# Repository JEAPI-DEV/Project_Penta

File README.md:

## Schematic and PCB Layers

- [Schematic](files/schematic.pdf)
- [PCB Front](files/pcbF.pdf)
- [PCB Back](files/pcbB.pdf)
- [PCB Inner Layer 1](files/pcbIn1.pdf)
- [PCB Inner Layer 2](files/pcbIn2.pdf)

## Here As Image Previews.

### Schematic 

### PCB Front

### PCB Inner Layer 1

### PCB Inner Layer 2

### PCB Back

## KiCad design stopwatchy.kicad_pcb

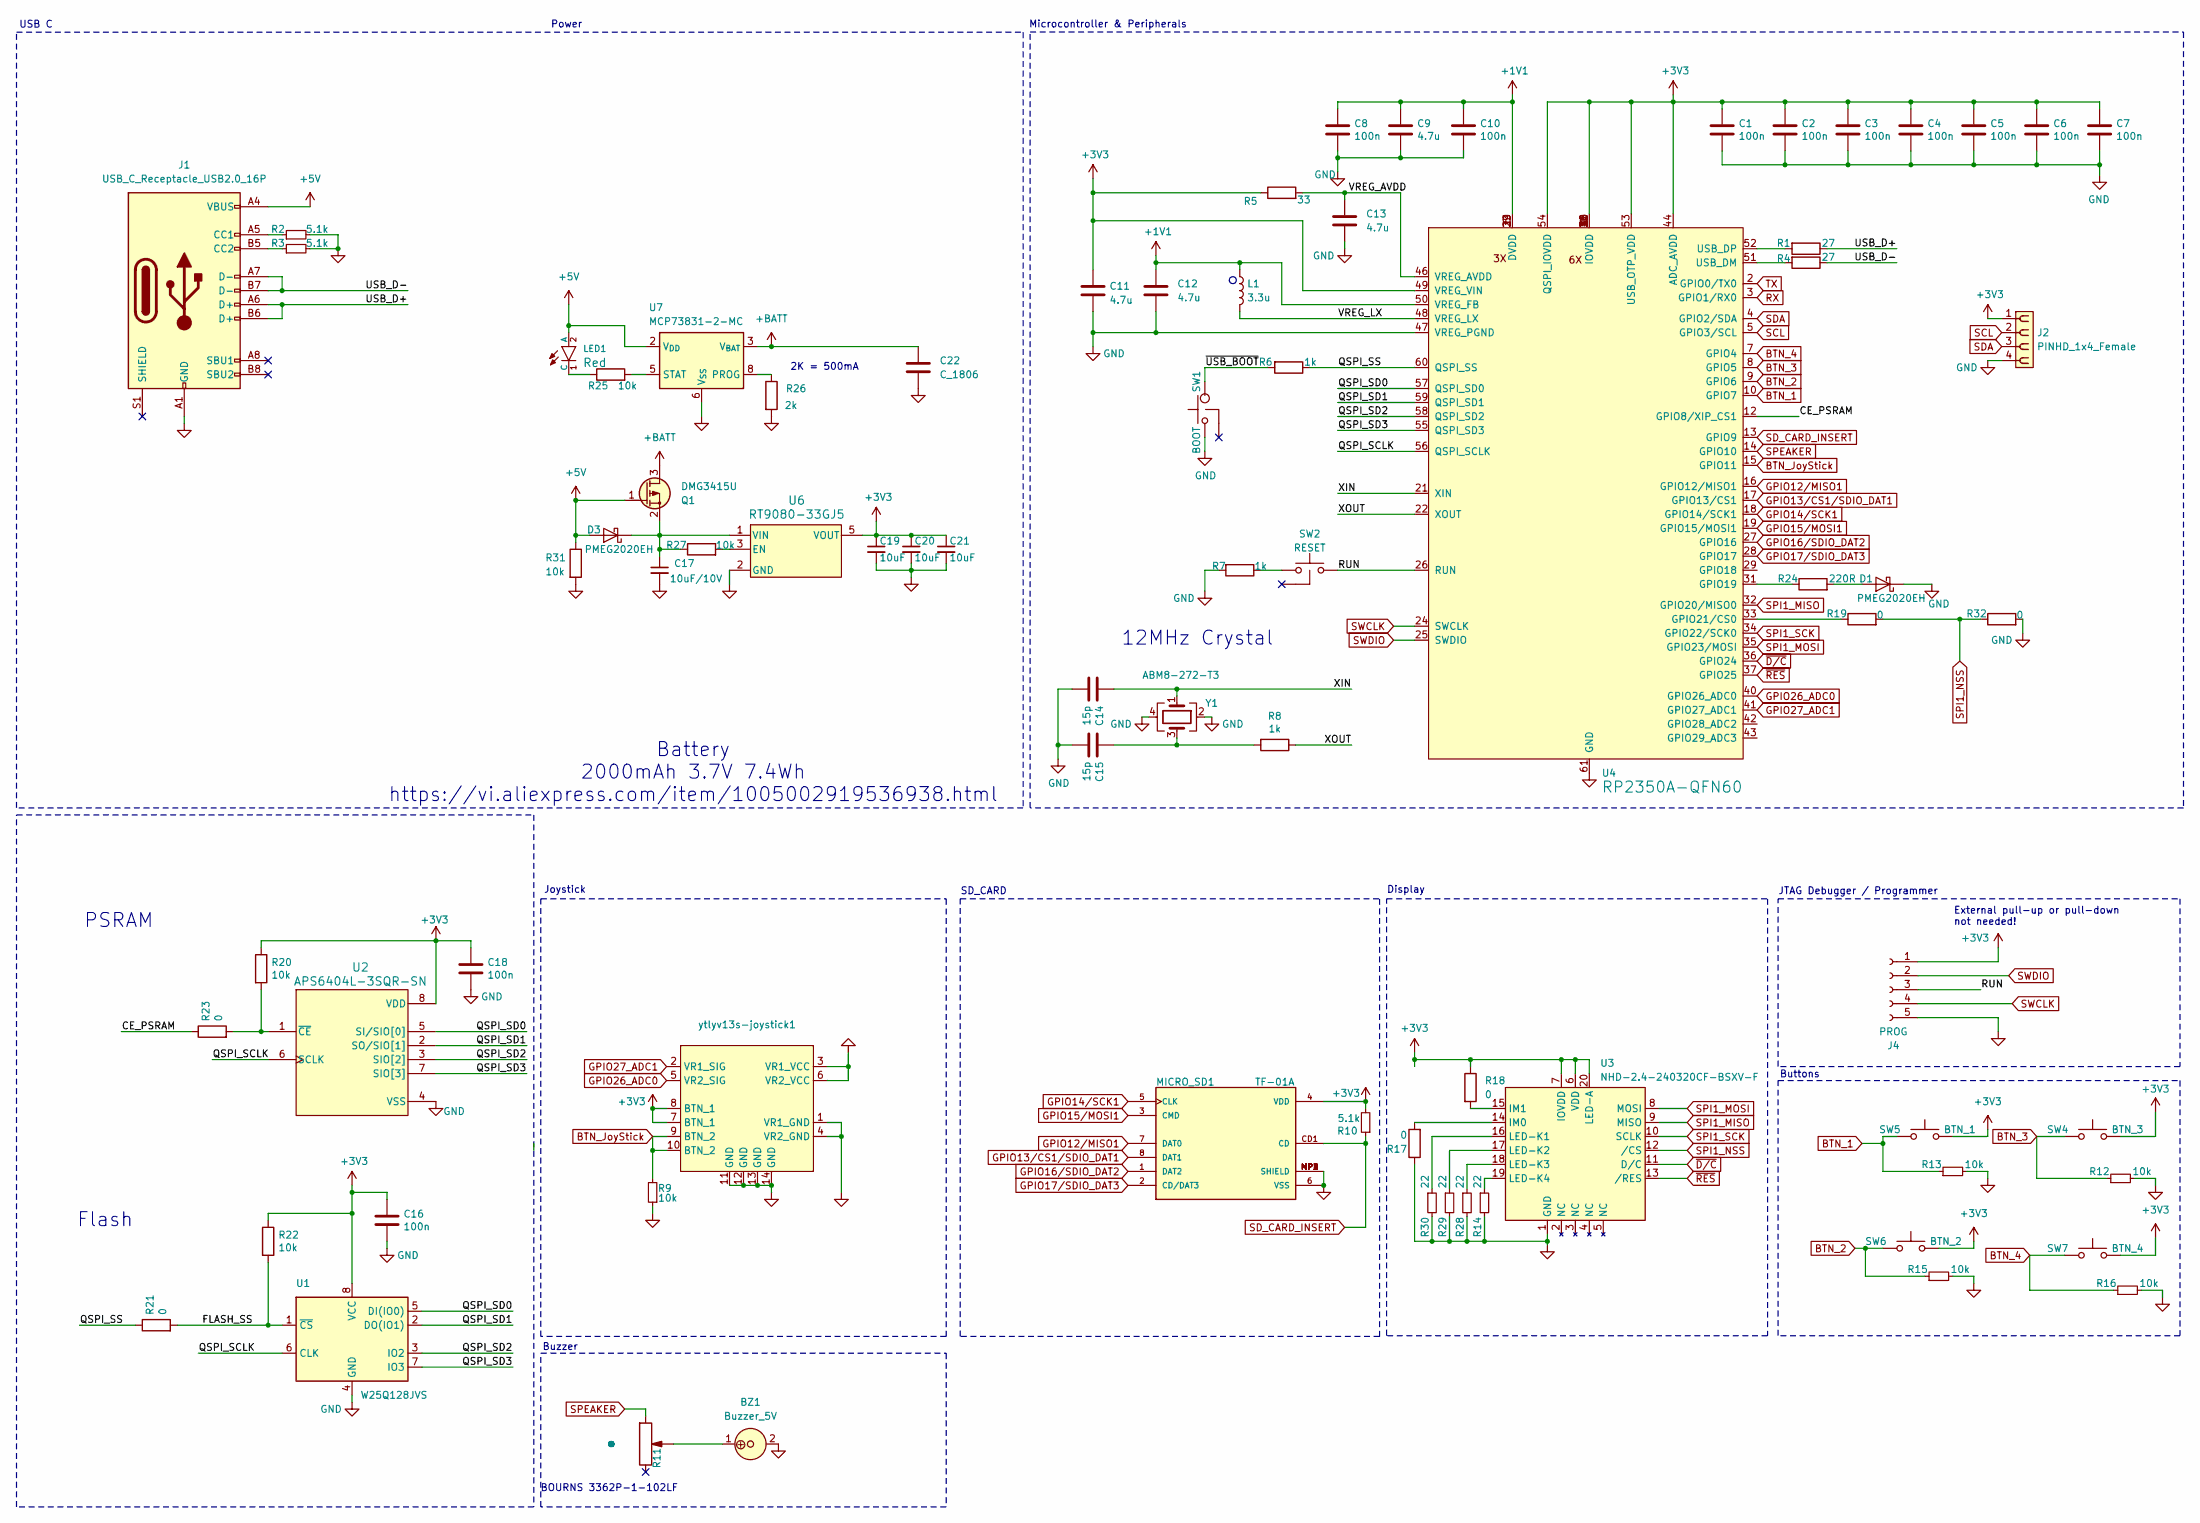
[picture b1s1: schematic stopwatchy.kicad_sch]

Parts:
BZ1: Buzzer_5V; Speaker_MLT-8530
C1, C2, C3, C4, C5, C6, C7, C8, C10, C16, C18: 100n; C_0402_1005Metric
C9: 4.7u; C_0402_1005Metric; LCSC C23687
C11, C12, C13: 4.7u; C_0402_1005Metric
C14, C15: 15p; C_0402_1005Metric
C17, C19, C20, C21: 10uF_0603_10V; C_0603; Part Number GRM188R61A106KE69D; JLCPCB ID C19702
C22: C_1806; C_1806_4516Metric
D1, D3: PMEG2020EH; D_SOD-123F
J1: USB_C_Receptacle_USB2.0_16P; USB_C_Receptacle_G-Switch_GT-USB-7010ASV
J2: PINHD_1x4_Female; PinSocket_1x04_P2.54mm_Horizontal
J4: PROG; PinHeader_2x03_P2.54mm_Vertical
L1: 3.3u; L_0603_1608Metric
LED1: Red_100mcd_0603; LED_0603_1608Metric; Part Number AP1608SRCPRV; lcsc C2899996
MICRO_SD1: TF-01A
Q1: DMG3415U; SOT-23
R1, R4: 27; R_0402_1005Metric
R2, R3, R10: 5.1k; R_0603_1608Metric; LCSC C25804
R5: 33; R_0402_1005Metric
R6, R7, R8: 1k; R_0402_1005Metric
R9, R12, R13, R15, R16: 10k; R_0603_1608Metric; LCSC C25804
R11: Volume; potentiometer_3362P
R14, R28, R29, R30: 22; R_0603_1608Metric; LCSC C22775
R17, R18, R19, R32: 0; R_0805_2012Metric
R20, R22: 10k; R_0402_1005Metric
R21, R23: 0; R_0402_1005Metric
R24: 220R_0603; R_0603; Part Number RC0603FR-07220RL; JLCPCB ID C8218
R25, R27, R31: 10k_0402; R_0402_1005Metric; Part Number RT0402FRE0710KL
R26: 2k_0603; R_0603
SW1: BOOT; SHOU HAN TS24CA
SW2: RESET; SHOU HAN TS24CA
SW4: BTN_3; SW_PUSH_6mm
SW5: BTN_1; SW_PUSH_6mm
SW6: BTN_2; SW_PUSH_6mm
SW7: BTN_4; SW_PUSH_6mm
U1: W25Q128JVS; SOIC-8_5.23x5.23mm_P1.27mm
U2: APS6404L-3SQR-SN; APS6404L-3SQR-SN_APY
U3: NHD-2.4-240320CF-BSXV-F
U4: RP2350A-QFN60; RP2350A_QFN-60_EP_7.75x7.75_Pitch0.4mm
U6: RT9080-33GJ5; TSOT-23-5_RIT
U7: MCP73831-2-MC; DFN-8-1EP_3x2mm_P0.5mm_EP1.7x1.4mm
Y1: ABM8-272-T3; Crystal_SMD_3225-4Pin_3.2x2.5mm
ytlyv13s-joystick1: joystick-ytlyv13s

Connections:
+1V1: C8.1, C9.1, C10.1, C12.1, L1.1, U4.6 (DVDD), U4.23 (DVDD), U4.39 (DVDD), U4.50 (VREG_FB)
+3V3: C1.1, C2.1, C3.1, C4.1, C5.1, C6.1, C7.1, C11.1, C16.1, C18.1, C19.1, C20.1, C21.1, J2.1, J4.1, MICRO_SD1.4 (VDD), R5.1, R10.2, R18.1, R20.1, R22.1, SW4.2, SW5.2, SW6.2, SW7.2, U1.8 (VCC), U2.8 (VDD), U3.6 (VDD), U3.7 (IOVDD), U3.20 (LED-A), U4.1 (IOVDD), U4.11 (IOVDD), U4.20 (IOVDD), U4.30 (IOVDD), U4.38 (IOVDD), U4.44 (ADC_AVDD), U4.45 (IOVDD), U4.49 (VREG_VIN), U4.53 (USB_OTP_VDD), U4.54 (QSPI_IOVDD), U6.5 (VOUT), ytlyv13s-joystick1.7 (BTN_1), ytlyv13s-joystick1.8 (BTN_1); also elsewhere on the board
+5V: D3.2 (A), J1.A4 (VBUS), J1.A9 (VBUS), J1.B4 (VBUS), J1.B9 (VBUS), LED1.2 (A), Q1.1 (G), R31.1, U7.1 (V_{DD}), U7.2 (V_{DD}); also elsewhere on the board
+BATT: C22.1, Q1.3 (D), U7.3 (V_{BAT}), U7.4 (V_{BAT})
/CE_PSRAM: R23.1, U4.12 (GPIO8/XIP_CS1)
/FLASH_SS: R21.2, R22.2, U1.1 (~CS)
/QSPI_SCLK: U1.6 (CLK), U2.6 (SCLK), U4.56 (QSPI_SCLK); also elsewhere on the board
/QSPI_SD0: U1.5 (DI(IO0)), U2.5 (SI/SIO[0]), U4.57 (QSPI_SD0); also elsewhere on the board
/QSPI_SD1: U1.2 (DO(IO1)), U2.2 (SO/SIO[1]), U4.59 (QSPI_SD1); also elsewhere on the board
/QSPI_SD2: U1.3 (IO2), U2.3 (SIO[2]), U4.58 (QSPI_SD2); also elsewhere on the board
/QSPI_SD3: U1.7 (IO3), U2.7 (SIO[3]), U4.55 (QSPI_SD3); also elsewhere on the board
/QSPI_SS: R6.1, R21.1, U4.60 (QSPI_SS)
/RUN: J4.3, SW2.2, U4.26 (RUN); also elsewhere on the board
/USB_D+: J1.A6 (D+), J1.B6 (D+), R1.1
/USB_D-: J1.A7 (D-), J1.B7 (D-), R4.1
/VREG_AVDD: C13.1, R5.2, U4.46 (VREG_AVDD)
/VREG_LX: L1.2, U4.48 (VREG_LX)
/XIN: C14.1, U4.21 (XIN), Y1.1
/XOUT: R8.1, U4.22 (XOUT)
/~USB_BOOT: R6.2, SW1.2; also elsewhere on the board
BTN_1: R13.1, SW5.1, U4.10 (GPIO7)
BTN_2: R15.1, SW6.1, U4.9 (GPIO6)
BTN_3: R12.1, SW4.1, U4.8 (GPIO5)
BTN_4: R16.1, SW7.1, U4.7 (GPIO4)
BTN_JoyStick: R9.2, U4.15 (GPIO11), ytlyv13s-joystick1.9 (BTN_2), ytlyv13s-joystick1.10 (BTN_2)
GND: BZ1.2, C1.2, C2.2, C3.2, C4.2, C5.2, C6.2, C7.2, C8.2, C9.2, C10.2, C11.2, C12.2, C13.2, C14.2, C15.2, C16.2, C17.2, C18.2, C19.2, C20.2, C21.2, C22.2, D1.1 (K), J1.A1 (GND), J1.A12 (GND), J1.B1 (GND), J1.B12 (GND), J2.4, J4.5, MICRO_SD1.6 (VSS), MICRO_SD1.MP1 (SHIELD), MICRO_SD1.MP2 (SHIELD), MICRO_SD1.MP3 (SHIELD), MICRO_SD1.MP4 (SHIELD), R2.2, R3.2, R7.2, R9.1, R12.2, R13.2, R14.2, R15.2, R16.2, R17.1, R26.2, R28.2, R29.2, R30.2, R31.2, R32.2, SW1.1, U1.4 (GND), U2.4 (VSS), U3.1 (GND), U4.47 (VREG_PGND), U4.61 (GND), U6.2 (GND), U7.6 (V_{SS}), Y1.2, Y1.4, ytlyv13s-joystick1.1 (VR1_GND), ytlyv13s-joystick1.3 (VR1_VCC), ytlyv13s-joystick1.4 (VR2_GND), ytlyv13s-joystick1.6 (VR2_VCC), ytlyv13s-joystick1.11 (GND), ytlyv13s-joystick1.12 (GND), ytlyv13s-joystick1.13 (GND), ytlyv13s-joystick1.14 (GND); also elsewhere on the board
GPIO12/MISO1: MICRO_SD1.7 (DAT0), U4.16 (GPIO12/MISO1)
GPIO13/CS1/SDIO_DAT1: MICRO_SD1.8 (DAT1), U4.17 (GPIO13/CS1)
GPIO14/SCK1: MICRO_SD1.5 (CLK), U4.18 (GPIO14/SCK1)
GPIO15/MOSI1: MICRO_SD1.3 (CMD), U4.19 (GPIO15/MOSI1)
GPIO16/SDIO_DAT2: MICRO_SD1.1 (DAT2), U4.27 (GPIO16)
GPIO17/SDIO_DAT3: MICRO_SD1.2 (CD/DAT3), U4.28 (GPIO17)
GPIO26_ADC0: U4.40 (GPIO26_ADC0), ytlyv13s-joystick1.5 (VR2_SIG)
GPIO27_ADC1: U4.41 (GPIO27_ADC1), ytlyv13s-joystick1.2 (VR1_SIG)
unnamed: C15.1, R8.2, Y1.3
unnamed: D1.2 (A), R24.2
unnamed: C17.1, D3.1 (K), Q1.2 (S), R27.1, U6.1 (VIN)
unnamed: J1.A5 (CC1), R2.1
unnamed: J1.B5 (CC2), R3.1
unnamed 39: LED1.1 (C), R25.1; also elsewhere on the board
unnamed 40: R7.1, SW2.1; also elsewhere on the board
unnamed: BZ1.1, R11.2 (b)
unnamed 42: R20.2, R23.2, U2.1 (~CE); also elsewhere on the board
unnamed: R17.2, U3.14 (IM0)
unnamed: R18.2, U3.15 (IM1)
unnamed: R30.1, U3.16 (LED-K1)
unnamed: R29.1, U3.17 (LED-K2)
unnamed: R28.1, U3.18 (LED-K3)
unnamed: R14.1, U3.19 (LED-K4)
unnamed: R24.1, U4.31 (GPIO19)
unnamed: R19.1, U4.33 (GPIO21/CS0)
unnamed: R4.2, U4.51 (USB_DM)
unnamed: R1.2, U4.52 (USB_DP)
unnamed: R27.2, U6.3 (EN)
unnamed: R26.1, U7.8 (PROG)
unnamed: R25.2, U7.5 (STAT)
RX: U4.3 (GPIO1/RX0)
SCL: J2.2, U4.5 (GPIO3/SCL)
SDA: J2.3, U4.4 (GPIO2/SDA)
SD_CARD_INSERT: MICRO_SD1.CD1 (CD), R10.1, U4.13 (GPIO9)
SPEAKER: R11.3 (c), U4.14 (GPIO10)
SPI1_MISO: U3.9 (MISO), U4.32 (GPIO20/MISO0)
SPI1_MOSI: U3.8 (MOSI), U4.35 (GPIO23/MOSI)
SPI1_NSS: R19.2, R32.1, U3.12 (/CS)
SPI1_SCK: U3.10 (SCLK), U4.34 (GPIO22/SCK0)
SWCLK: J4.4, U4.24 (SWCLK)
SWDIO: J4.2, U4.25 (SWDIO)
TX: U4.2 (GPIO0/TX0)
~D/C: U3.11 (D/C), U4.36 (GPIO24)
~RES: U3.13 (/RES), U4.37 (GPIO25)

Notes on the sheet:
Display
External pull-up or pull-down not needed!
Microcontroller & Peripherals
SD_CARD
Power
Flash
2K = 500mA
PSRAM
Buttons
JTAG Debugger / Programmer
12MHz Crystal
Joystick
Buzzer
Battery 2000mAh 3.7V 7.4Wh https://vi.aliexpress.com/item/1005002919536938.html
BOURNS 3362P-1-102LF
USB C

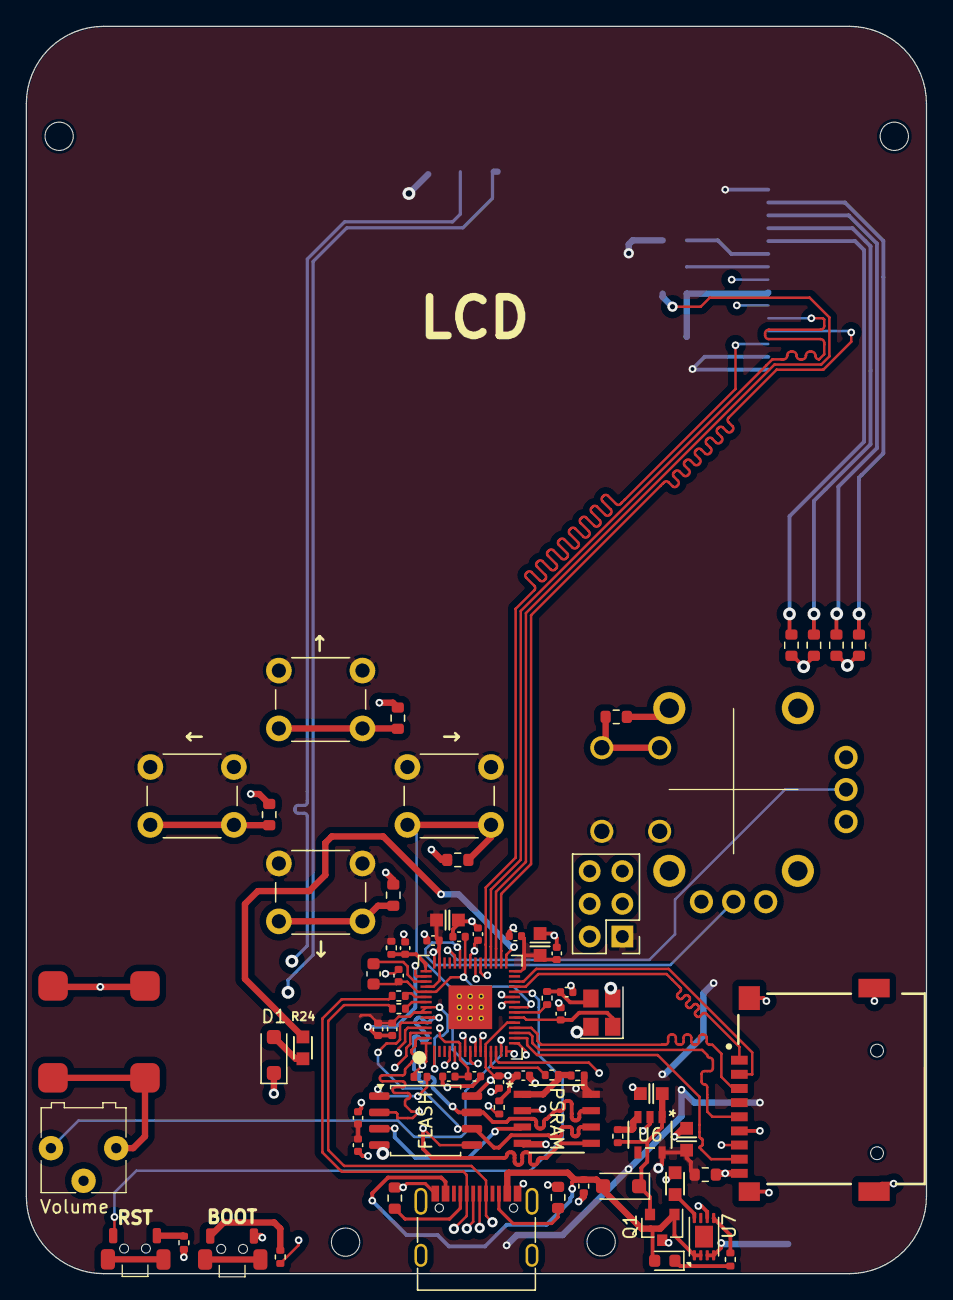
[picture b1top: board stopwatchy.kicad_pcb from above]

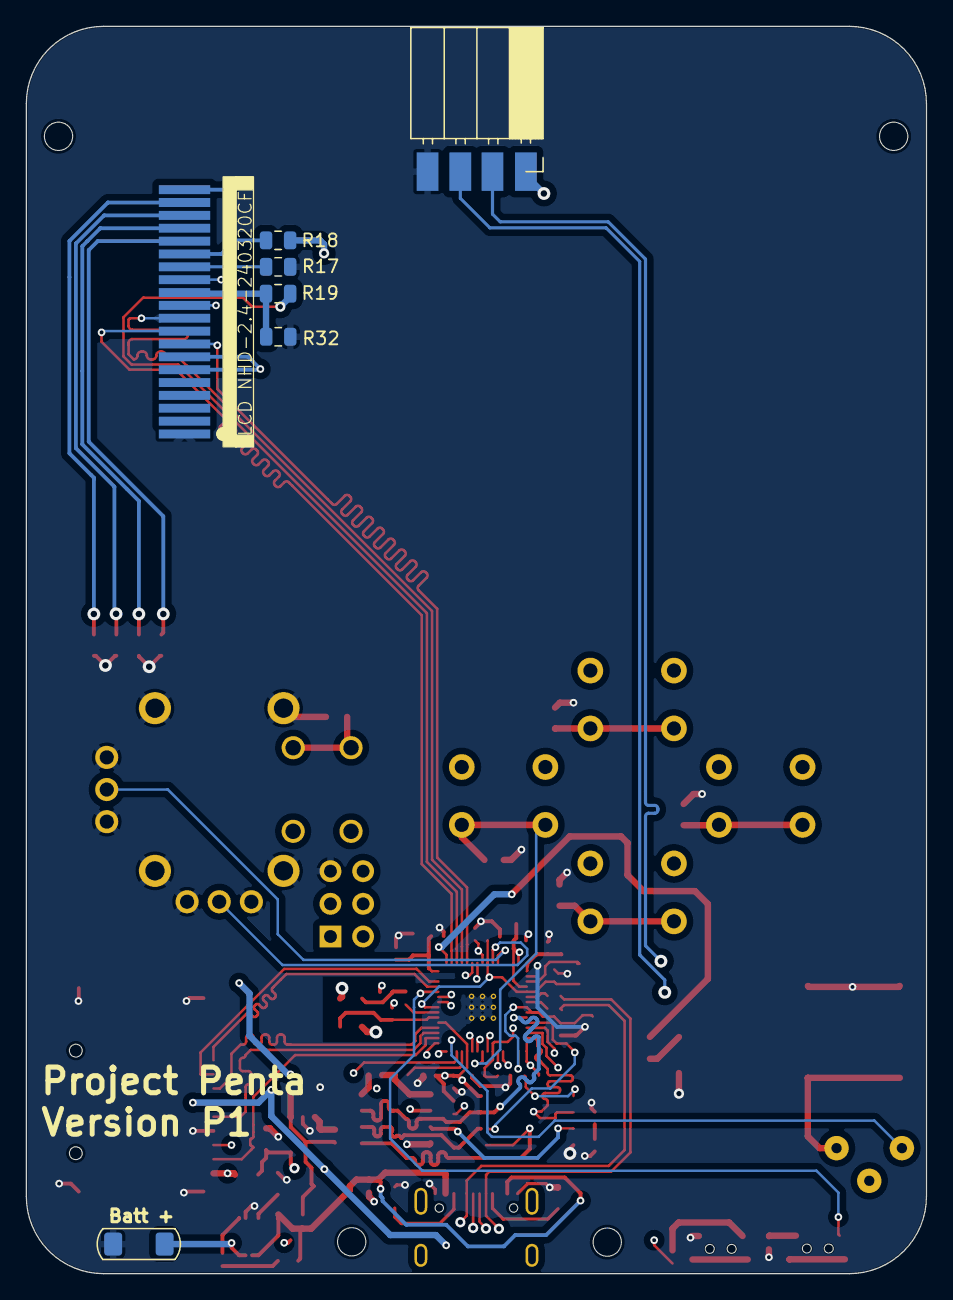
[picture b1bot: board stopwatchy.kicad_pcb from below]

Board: 4 copper layers, 70.0 x 97.0 mm, 78 parts (7 on the bottom side), 68 nets.

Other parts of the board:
BOOT: BOOT; SHOU HAN TS24CA
CH: Red_100mcd_0603; LED_0603_1608Metric
PSRAM: APS6404L-3SQR-SN; APS6404L-3SQR-SN_APY
RST: RESET; SHOU HAN TS24CA

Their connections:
+3V3: PSRAM.8 (VDD); also elsewhere on the board
+5V: CH.2 (A); also elsewhere on the board
/QSPI_SCLK: PSRAM.6 (SCLK); also elsewhere on the board
/QSPI_SD0: PSRAM.5 (SI/SIO[0]); also elsewhere on the board
/QSPI_SD1: PSRAM.2 (SO/SIO[1]); also elsewhere on the board
/QSPI_SD2: PSRAM.3 (SIO[2]); also elsewhere on the board
/QSPI_SD3: PSRAM.7 (SIO[3]); also elsewhere on the board
/RUN: RST.2; also elsewhere on the board
/~USB_BOOT: BOOT.2; also elsewhere on the board
GND: BOOT.1, PSRAM.4 (VSS); also elsewhere on the board
unnamed 39: CH.1 (C); also elsewhere on the board
unnamed 40: RST.1; also elsewhere on the board
unnamed 42: PSRAM.1 (~CE); also elsewhere on the board

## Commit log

2025-07-06 Init
2025-07-06 Added readme and pdfs+pngs.
2025-07-06 Renamed png and fixed README
2025-07-06 remove
2025-07-06 fix schematic
2025-07-06 fix schematic2
